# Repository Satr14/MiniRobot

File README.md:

Tugas Pemrogaman Sistem Mekatronik

-> MINI ROBOT <-

-> Arduino Nano Wall Follower <-

Not Use : RST,D8,D9,REF

Button
	RST : reset

Switch Komunikasi Antar Arduino
	1: RX -> TX
	2: TX -> RX

Modul wifi ESP diganti dengan modul Bluetooth
	D10 (RX/PWM) : RX
	D11 (TX/Mosi1) : TX
	3V3	: Vcc dan Ch_Pd/En
	GND	: GND dan GPIO 0
	Not Use : (reset),(GPIO 2)

IMU 6050
	3V3 : pin 1 (3v3)
	A4 : pin 4 (SDA)
	A5 : pin 3 (SCL)
	no use : sisanya 
Yang digunakan untuk heading hanya sumbu z saja

Ultrasonic Kanan 
	Trig : D7
	Echo : D6
	
Ultrasonic Kiri
	Trig : D3
	Echo : D2

Ultrasonic Depan
	Trig : D5
	Echo : D4

-> Arduino Nano Line Follower <-

Not Use : RST,REF,A7

LCD I2C
	Address: 0X27
	A4 : SDA
	A5 : SCL

Driver Motor (HW-166)
	PWMA : D3
	AIN2 : D2
	AIN1 : D4
	STBY : D9
	BIN1 : D7
	BIN2 : D8
	PWMB : D5

Buzzer 
	Transistor : D6

Button
	RST : reset
	D12(1) : D12
	D11(2) : D11
	D13(3) : D13

Led
	- : D10

Led & Infrared
	infrared 1 : A0
	infrared 2 : A1
	infrared 3 : A2
	infrared 4 : A3
	infrared 5 : A6
	
Pembacaan Putih <720
Pembacaan Hitam >880

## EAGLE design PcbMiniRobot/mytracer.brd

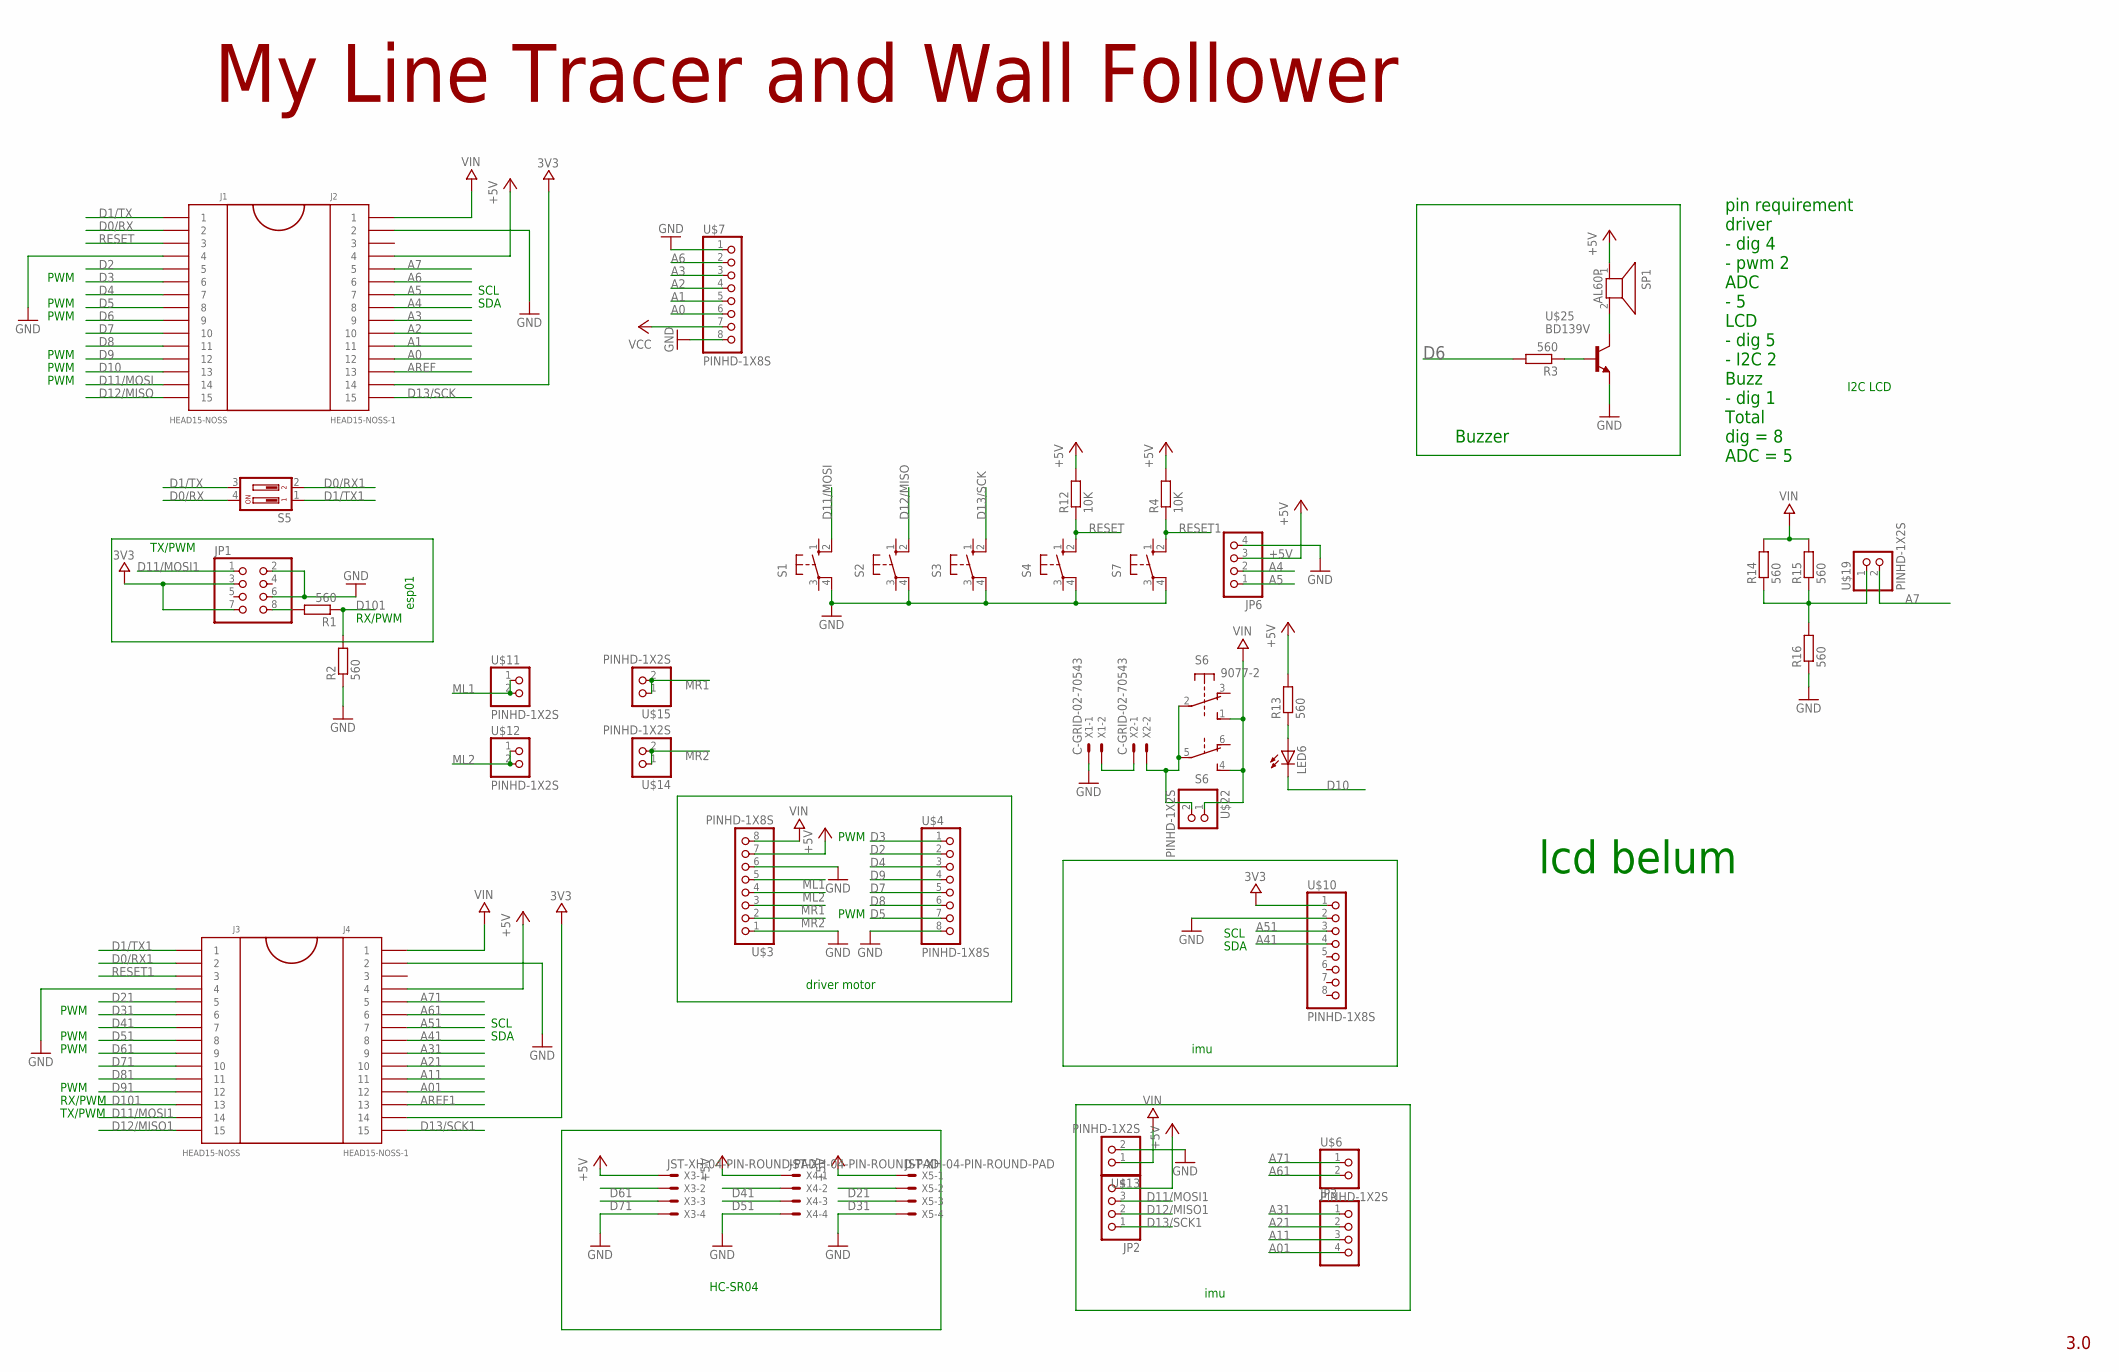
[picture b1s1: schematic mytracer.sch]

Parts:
J1, J3: HEAD15-NOSS
J2, J4: HEAD15-NOSS-1
JP1: PINHD-2X4; 2X04
JP2, JP3, JP6: PINHD-1X4; 1X04
LED6: LED3MM
R1, R2, R3, R13, R14, R15, R16: 560; M1206
R4, R12: 10K; M1206
S1, S2, S3, S4, S7: 10-XX; B3F-10XX
S5: DIP02YL
S6: 9077-2
SP1: AL60P
U$3, U$4, U$7, U$10: PINHD-1X8S; 1X08S
U$6, U$11, U$12, U$13, U$14, U$15, U$19, U$22: PINHD-1X2S; 1X02S
U$25: BD139V; TO126V
X1, X2: C-GRID-02-70543; 70543-02
X3, X4, X5: JST-XH-04-PIN-ROUND-PAD; JST-XH-04-PACKAGE-ROUND-PAD

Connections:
3V3: J2.14, J4.14, JP1.3, JP1.7, U$10.1
+5V: J2.4, J4.4, JP2.4, JP6.3, R4.2, R12.2, R13.2, SP1.1, U$3.7, X3.1, X4.1, X5.1
A0: J2.12, U$7.6
A1: J2.11, U$7.5
A01: J4.12, JP3.4
A2: J2.10, U$7.4
A3: J2.9, U$7.3
A4: J2.8, JP6.2
A5: J2.7, JP6.1
A6: J2.6, U$7.2
A7: J2.5, U$19.2
A11: J4.11, JP3.3
A21: J4.10, JP3.2
A31: J4.9, JP3.1
A41: J4.8, U$10.4
A51: J4.7, U$10.3
A61: J4.6, U$6.2
A71: J4.5, U$6.1
AREF: J2.13
AREF1: J4.13
D0/RX: J1.2, S5.4
D0/RX1: J3.2, S5.2
D1/TX: J1.1, S5.3
D1/TX1: J3.1, S5.1
D2: J1.5, U$4.2
D3: J1.6, U$4.1
D4: J1.7, U$4.3
D5: J1.8, U$4.7
D6: J1.9, R3.2
D7: J1.10, U$4.5
D8: J1.11, U$4.6
D9: J1.12, U$4.4
D10: J1.13, LED6.K (C)
D11/MOSI: J1.14, S1.2 (S1)
D11/MOSI1: J3.14, JP1.1, JP2.3
D12/MISO: J1.15, S2.2 (S1)
D12/MISO1: J3.15, JP2.2
D13/SCK: J2.15, S3.2 (S1)
D13/SCK1: J4.15, JP2.1
D21: J3.5, X5.2
D31: J3.6, X5.3
D41: J3.7, X4.2
D51: J3.8, X4.3
D61: J3.9, X3.2
D71: J3.10, X3.3
D81: J3.11
D91: J3.12
D101: J3.13, R1.1, R2.2
GND: J1.4, J2.2, J3.4, J4.2, JP1.2, JP1.6, JP6.4, R2.1, R16.1, S1.4 (P1), S2.4 (P1), S3.4 (P1), S4.4 (P1), S7.4 (P1), U$3.1, U$3.6, U$4.8, U$7.1, U$7.8, U$10.2, U$13.2, U$25.1 (E), X1.1, X3.4, X4.4, X5.4
ML1: U$3.5, U$11.1, U$11.2
ML2: U$3.4, U$12.1, U$12.2
MR1: U$3.3, U$15.1, U$15.2
MR2: U$3.2, U$14.1, U$14.2
unnamed: R14.1, R15.1, R16.2, U$19.1
unnamed: JP1.8, R1.2
unnamed: X1.2, X2.1
unnamed: S6.2, S6.5, U$22.2, X2.2
unnamed: LED6.A, R13.1
unnamed: R3.1, U$25.3 (B)
unnamed: SP1.2, U$25.2 (C)
RESET: J1.3, R12.1, S4.2 (S1)
RESET1: J3.3, R4.1, S7.2 (S1)
VCC: U$7.7
VIN: J2.1, J4.1, R14.2, R15.2, S6.1 (S), S6.4 (S), U$3.8, U$13.1, U$22.1

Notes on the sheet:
My Line Tracer and Wall Follower
3.0
Buzzer
pin requirement driver - dig 4 - pwm 2 ADC - 5 LCD - dig 5 - I2C 2 Buzz - dig 1 Total dig = 8 ADC = 5
SDA
SCL
PWM
I2C LCD
esp01
RX/PWM
TX/PWM
driver motor
imu
HC-SR04
lcd belum

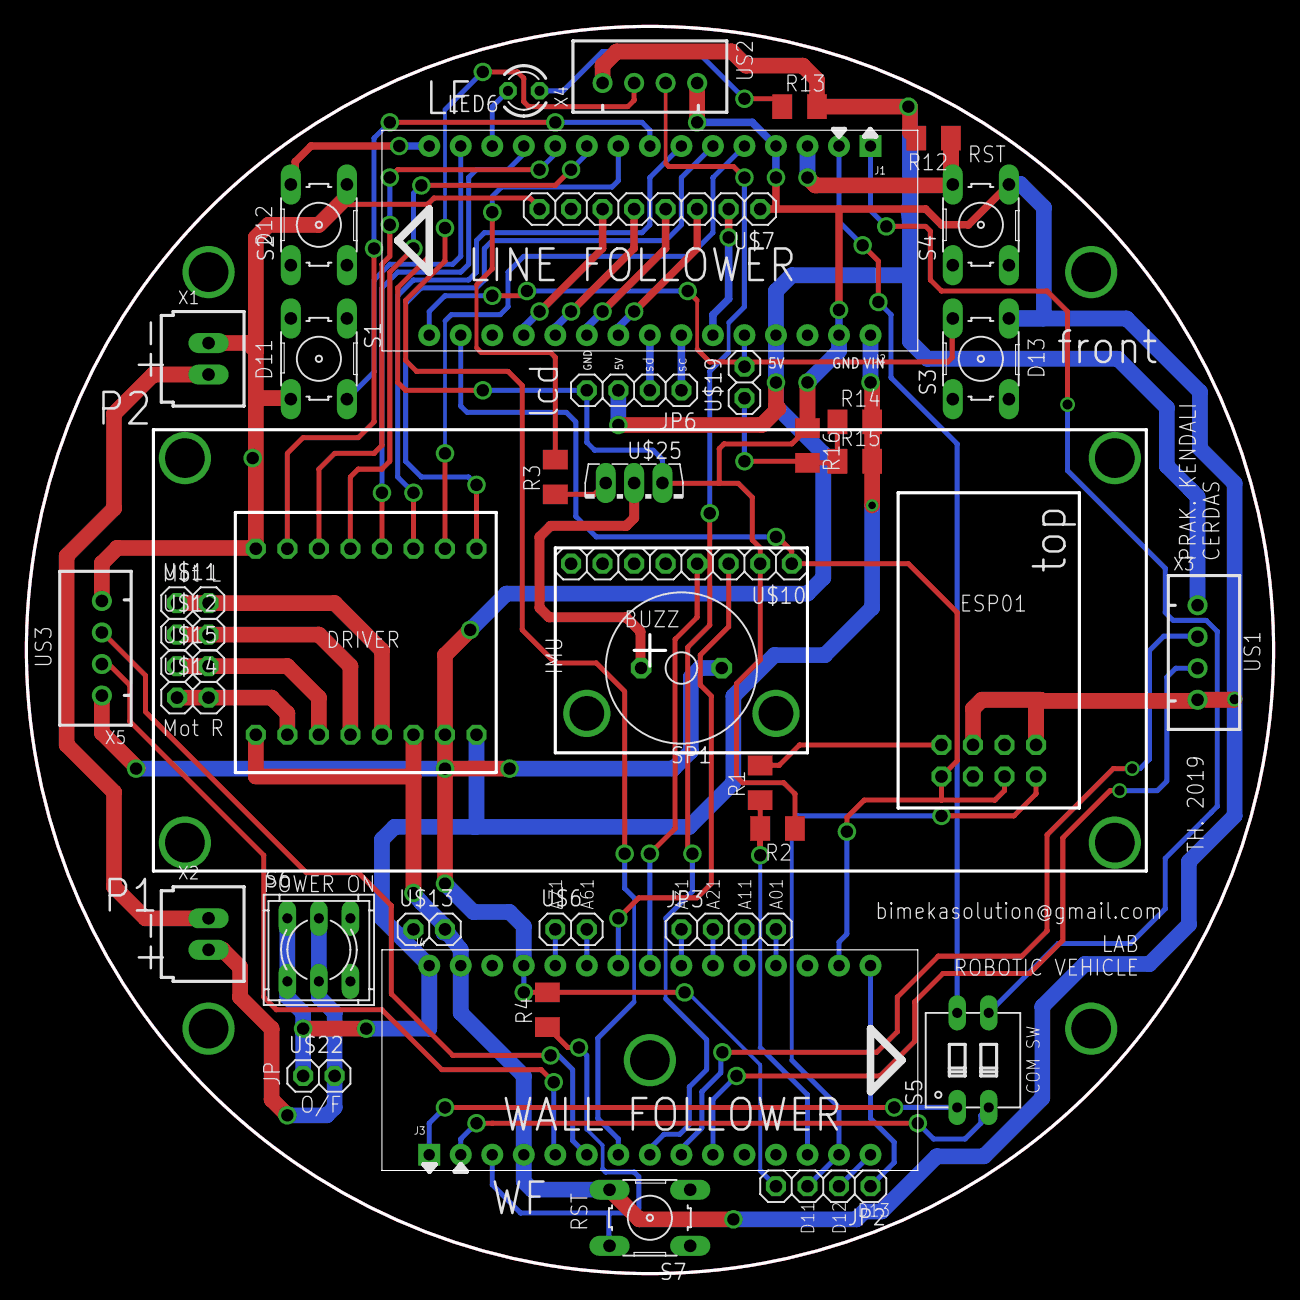
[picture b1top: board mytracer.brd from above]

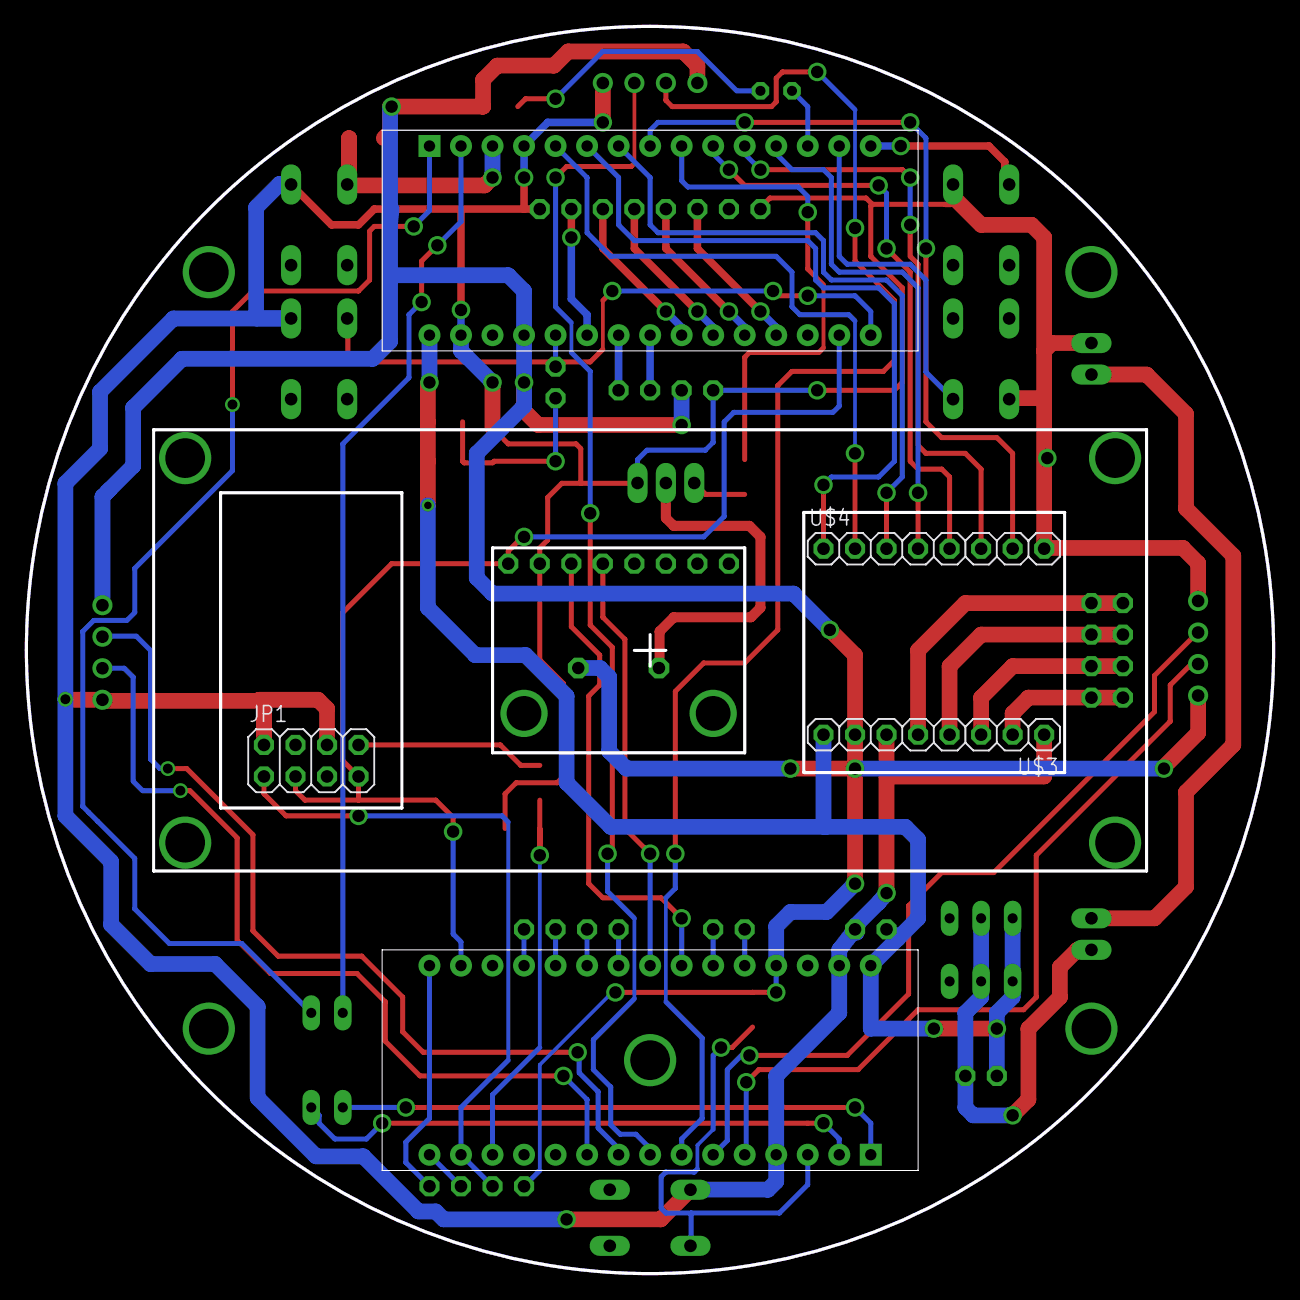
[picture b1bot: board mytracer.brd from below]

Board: 2 copper layers, 100.5 x 100.5 mm, 44 parts (3 on the bottom side), 59 nets.

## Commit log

2024-11-21 Add .gitignore, extensions, platformio.ini, and README files for SlaveMiniRobot and MasterMiniRobot
2024-11-22 Add configuration files and documentation for SlaveMiniRobot and MasterMiniRobot
2024-11-26 Implement line detection and navigation logic for SlaveMiniRobot
2024-11-26 I/O List Mini Robot PENS
